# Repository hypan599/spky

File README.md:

# SPKY
This is a series of split, ergonomics keyboard that I designed and built.

I've beed play with different combinations of hardware and software with each version.

## SPKYv1
This is a split, column stagger, wireless build with PCB plate.

The layout was heavily inspired from other split keyboards, like [dygma defy](https://dygma.com/pages/defy) and the [moonlander](https://www.zsa.io/moonlander).

## SPKYv2
This is a row stagger, wired keyboard. One with MX switch and another version with choc switch.
MX version:

Choc version:

## SPKYv3
This is a 3D printed, hand wired keyboard, with slightly altered layout from spkyv1.

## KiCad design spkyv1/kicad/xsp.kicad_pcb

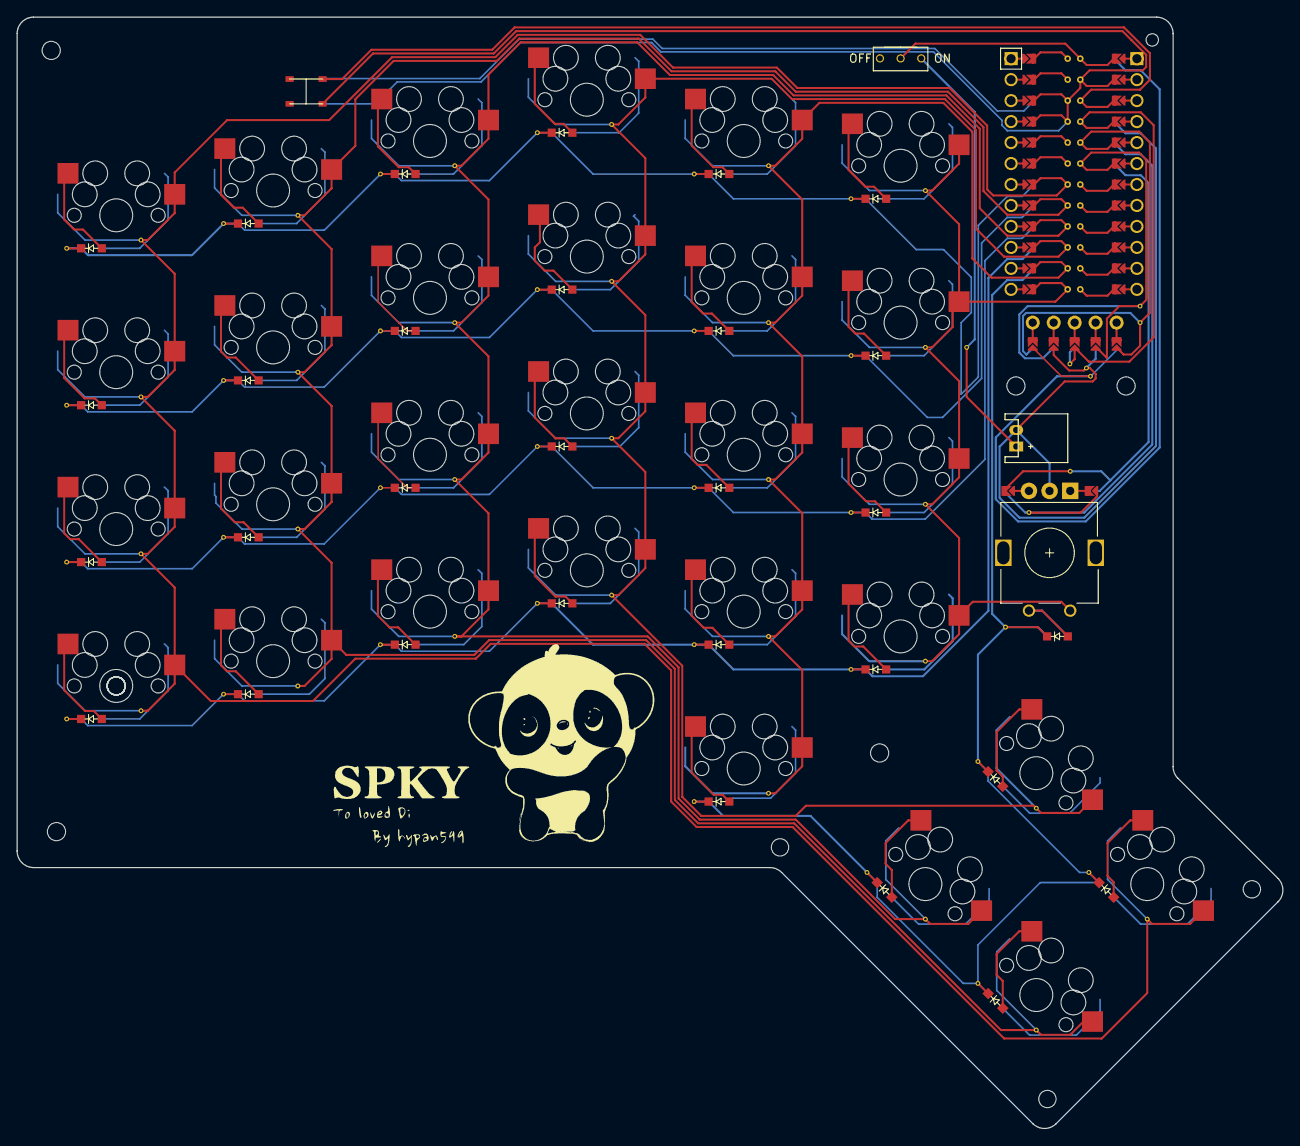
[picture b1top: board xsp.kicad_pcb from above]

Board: 2 copper layers, 153.3 x 134.6 mm, 67 parts (0 on the bottom side), 51 nets.

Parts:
B1, B2: RESET; SW_TACT_ALPS_SKQGABE010
D1, D2, D3, D4, D5, D6, D7, D8, D9, D10, D11, D12, D13, D14, D15, D16, D17, D18, D19, D20, D21, D22, D23, D24, D25, D26, D27, D28, D29, D30: ComboDiode
Hole2333: MountingHole_2.1mm
JST1: JST_PH_S2B-PH-K_02x2.00mm_Angled
MCU1: ProMicro
OLED1: OLED_headers
ROT1: rotary_encoder
S1, S2, S3, S4, S5, S6, S7, S8, S9, S10, S11, S12, S13, S14, S15, S16, S17, S18, S19, S20, S21, S22, S23, S24, S25, S26, S27, S28, S29: MX
T1: SPDT_C128955

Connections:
GND: B1.2, B2.2, JST1.2, MCU1.2, MCU1.21, MCU1.22, OLED1.1, OLED1.3, OLED1.V2, ROT1.C
P1: MCU1.24, OLED1.0, OLED1.4, OLED1.V3
P2: MCU1.20, ROT1.A, ROT1.V2
P3: MCU1.19, ROT1.B, ROT1.V1
P4: MCU1.18, S1.1, S2.1, S3.1, S4.1, S29.1
P5: MCU1.17, S5.1, S6.1, S7.1, S8.1, S28.1
P6: MCU1.16, S9.1, S10.1, S11.1, S12.1, S26.1
P7: MCU1.15, S13.1, S14.1, S15.1, S16.1, S27.1
P8: MCU1.14, S17.1, S18.1, S19.1, S20.1, S21.1
P9: MCU1.13, ROT1.1, S22.1, S23.1, S24.1, S25.1
P14: D1.1, D5.1, D9.1, D13.1, D18.1, D22.1, MCU1.10
P15: D2.1, D6.1, D10.1, D14.1, D19.1, D23.1, MCU1.9
P16: D17.1, D26.1, D27.1, D28.1, D29.1, D30.1, MCU1.11
P18: D3.1, D7.1, D11.1, D15.1, D20.1, D24.1, MCU1.8
P19: D4.1, D8.1, D12.1, D16.1, D21.1, D25.1, MCU1.7
P20: MCU1.6, OLED1.1, OLED1.3, OLED1.V4
P21: MCU1.5, OLED1.0, OLED1.4, OLED1.V5
R1: D30.2, ROT1.2
RAW: MCU1.1, T1.2
RST: B1.1, B2.1, MCU1.3
VCC: MCU1.4, OLED1.2, OLED1.V1
home_second: D29.2, S29.2
home_thumb: D28.2, S28.2
index_bottom: D17.2, S17.2
index_home: D18.2, S18.2
index_num: D20.2, S20.2
index_thumb: D21.2, S21.2
index_top: D19.2, S19.2
inner_bottom: D22.2, S22.2
inner_home: D23.2, S23.2
inner_num: D25.2, S25.2
inner_top: D24.2, S24.2
middle_bottom: D13.2, S13.2
middle_home: D14.2, S14.2
middle_num: D16.2, S16.2
middle_top: D15.2, S15.2
near_second: D27.2, S27.2
near_thumb: D26.2, S26.2
pinky_bottom: D5.2, S5.2
pinky_home: D6.2, S6.2
pinky_num: D8.2, S8.2
pinky_top: D7.2, S7.2
pos: JST1.1, T1.3
ring_bottom: D9.2, S9.2
ring_home: D10.2, S10.2
ring_num: D12.2, S12.2
ring_top: D11.2, S11.2
tab_bottom: D1.2, S1.2
tab_home: D2.2, S2.2
tab_num: D4.2, S4.2
tab_top: D3.2, S3.2

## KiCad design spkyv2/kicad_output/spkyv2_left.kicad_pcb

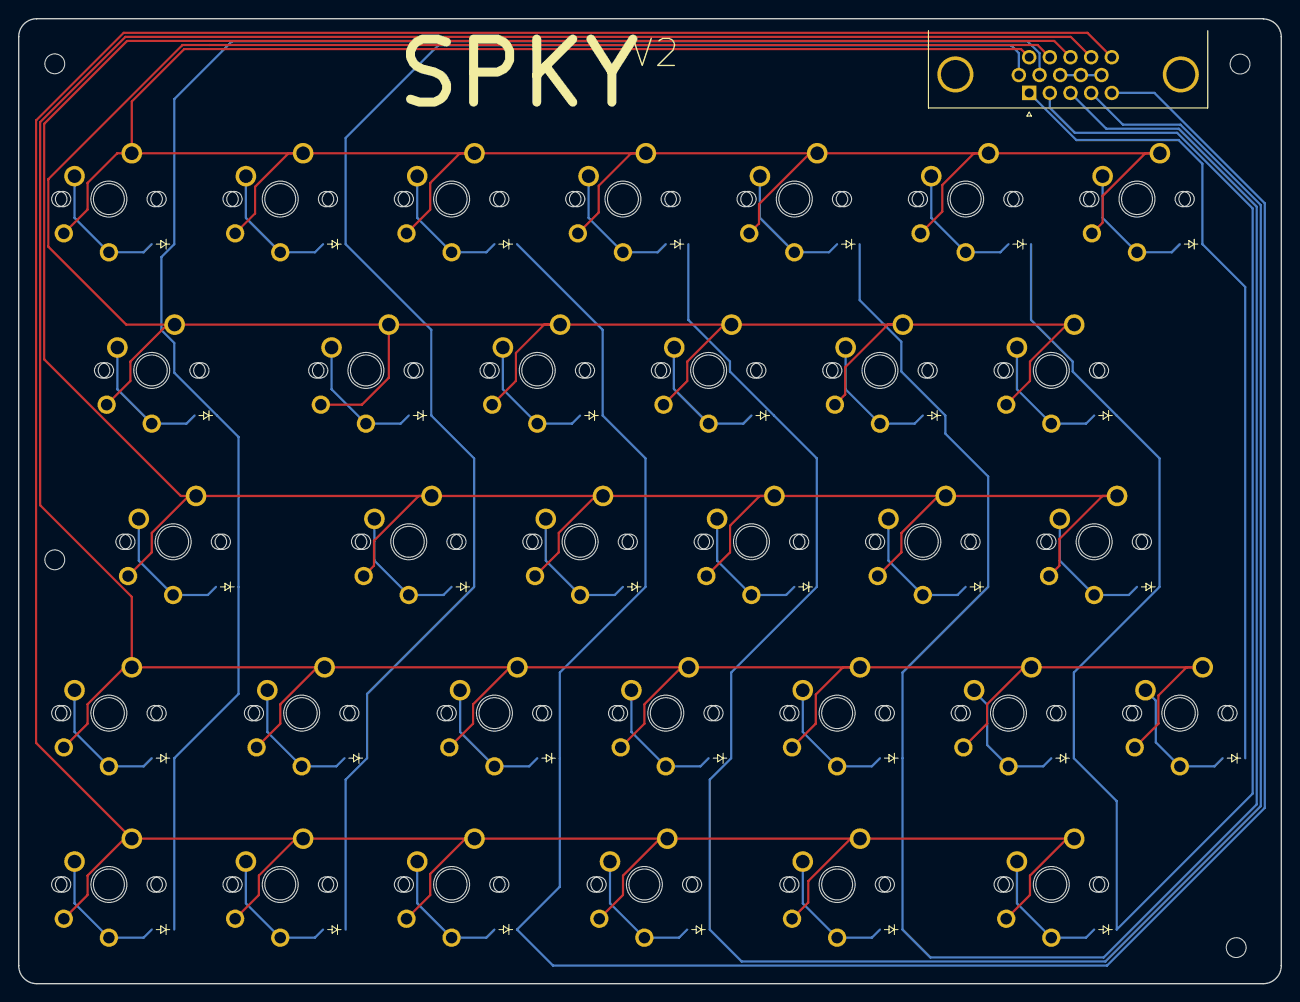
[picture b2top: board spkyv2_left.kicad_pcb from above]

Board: 2 copper layers, 140.0 x 107.0 mm, 96 parts (0 on the bottom side), 44 nets.

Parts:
D1, D2, D3, D4, D5, D6, D7, D8, D9, D10, D11, D12, D13, D14, D15, D16, D17, D18, D19, D20, D21, D22, D23, D24, D25, D26, D27, D28, D29, D30, D31, D32: ComboDiode
S1, S3, S5, S7, S9, S11, S13, S15, S17, S19, S21, S23, S25, S27, S29, S31, S33, S35, S37, S39, S41, S43, S45, S47, S49, S51, S53, S55, S57, S59, S61, S63: MX
S2, S4, S6, S8, S10, S12, S14, S16, S18, S20, S22, S24, S26, S28, S30, S32, S34, S36, S38, S40, S42, S44, S46, S48, S50, S52, S54, S56, S58, S60, S62, S64: PG1350

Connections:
P0: S15.1, S16.1, S17.1, S18.1, S19.1, S20.1, S21.1, S22.1, S23.1, S24.1, S25.1, S26.1
P1: S1.1, S2.1, S3.1, S4.1, S5.1, S6.1, S7.1, S8.1, S9.1, S10.1, S11.1, S12.1, S13.1, S14.1
P2: S27.1, S28.1, S29.1, S30.1, S31.1, S32.1, S33.1, S34.1, S35.1, S36.1, S37.1, S38.1
P3: S39.1, S40.1, S41.1, S42.1, S43.1, S44.1, S45.1, S46.1, S47.1, S48.1, S49.1, S50.1, S51.1, S52.1
P4: S53.1, S54.1, S55.1, S56.1, S57.1, S58.1, S59.1, S60.1, S61.1, S62.1, S63.1, S64.1
P14: D6.1, D13.1, D19.1, D25.1, D32.1
P15: D5.1, D12.1, D18.1, D24.1, D31.1
P16: D7.1, D26.1
P18: D4.1, D11.1, D17.1, D23.1, D30.1
P19: D3.1, D10.1, D16.1, D22.1, D29.1
P20: D2.1, D9.1, D15.1, D21.1, D28.1
P21: D1.1, D8.1, D14.1, D20.1, D27.1
asdf_edc: D17.2, S33.2, S34.2
asdf_qaz: D15.2, S29.2, S30.2
asdf_rfv: D18.2, S35.2, S36.2
asdf_tgb: D19.2, S37.2, S38.2
asdf_tilda: D14.2, S27.2, S28.2
asdf_wsx: D16.2, S31.2, S32.2
ctrl_edc: D30.2, S59.2, S60.2
ctrl_qaz: D28.2, S55.2, S56.2
ctrl_rfv: D31.2, S61.2, S62.2
ctrl_tgb: D32.2, S63.2, S64.2
ctrl_tilda: D27.2, S53.2, S54.2
ctrl_wsx: D29.2, S57.2, S58.2
number_edc: D4.2, S7.2, S8.2
number_qaz: D2.2, S3.2, S4.2
number_rfv: D5.2, S9.2, S10.2
number_six: D7.2, S13.2, S14.2
number_tgb: D6.2, S11.2, S12.2
number_tilda: D1.2, S1.2, S2.2
number_wsx: D3.2, S5.2, S6.2
qwer_edc: D11.2, S21.2, S22.2
qwer_qaz: D9.2, S17.2, S18.2
qwer_rfv: D12.2, S23.2, S24.2
qwer_tgb: D13.2, S25.2, S26.2
qwer_tilda: D8.2, S15.2, S16.2
qwer_wsx: D10.2, S19.2, S20.2
zxcv_edc: D23.2, S45.2, S46.2
zxcv_qaz: D21.2, S41.2, S42.2
zxcv_rfv: D24.2, S47.2, S48.2
zxcv_six: D26.2, S51.2, S52.2
zxcv_tgb: D25.2, S49.2, S50.2
zxcv_tilda: D20.2, S39.2, S40.2
zxcv_wsx: D22.2, S43.2, S44.2

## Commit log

2024-10-29 add images for v1 and v2
2024-10-29 add artifacts for v1 and v2
2024-11-01 add image for spkyv3
